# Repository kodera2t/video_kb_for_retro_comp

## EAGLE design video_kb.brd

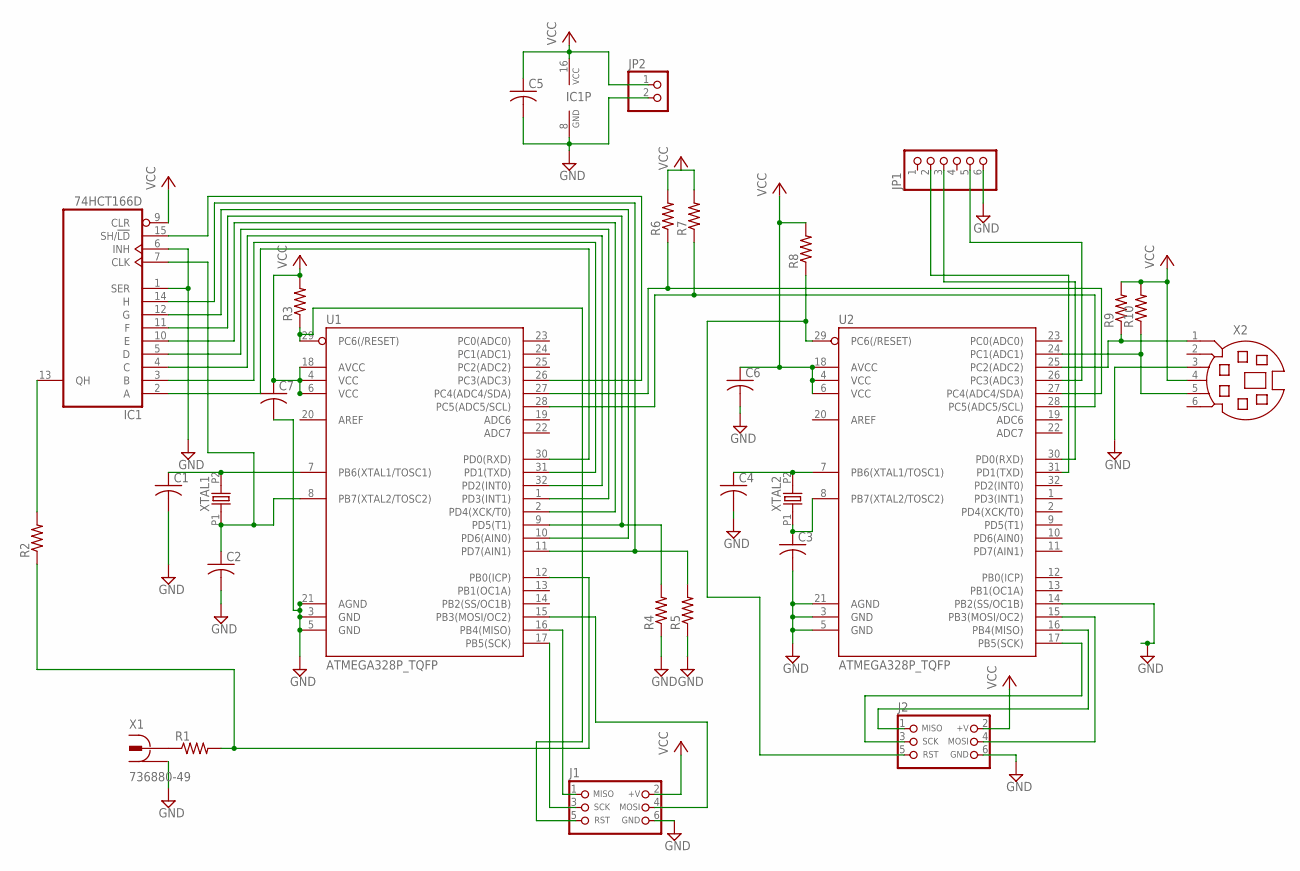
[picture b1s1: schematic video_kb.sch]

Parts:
C1, C2, C3, C4, C5, C6, C7: C-USC0603K; C0603K
IC1: 74HCT166D; SO16
J1, J2: CON_HEADER_PRG_AVR_ICSP-PTH; HEADER_PRG_2X03
JP1: HEADER-1X6; 1X06_OVAL
JP2: HEADER-1X2; 1X02_OVAL
R1, R2, R3, R4, R5, R6, R7, R8, R9, R10: R-US_R0603; R0603
U1, U2: ATMEGA328P_TQFP; TQFP32-08
X1: 736880-49
X2: MD06S; MDIN06S
XTAL1, XTAL2: OSC-XTAL-HC-49U-PTH; HC-49U-PTH

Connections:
GND: C1.2, C2.2, C3.2, C4.2, C5.2, C6.2, C7.2, IC1.1 (SER), IC1.6 (INH), IC1.8 (GND), J1.6 (GND), J2.6 (GND), JP1.6, JP2.2, R4.1, R5.1, U1.3 (GND), U1.5 (GND), U1.21 (AGND), U2.3 (GND), U2.5 (GND), U2.14 (PB2(SS/OC1B)), U2.21 (AGND), X1.1, X1.1@1 (1), X1.1@2 (1), X2.3
unnamed: C2.1, IC1.7 (CLK), U1.8 (PB7(XTAL2/TOSC2)), XTAL1.P1 (1)
unnamed: C1.1, U1.7 (PB6(XTAL1/TOSC1)), XTAL1.P2 (2)
unnamed: IC1.4 (C), U1.32 (PD2(INT0))
unnamed: IC1.5 (D), U1.1 (PD3(INT1))
unnamed: R1.2, R2.1, U1.12 (PB0(ICP))
unnamed: R1.1, X1.2
unnamed: IC1.13 (QH), R2.2
unnamed: IC1.10 (E), U1.2 (PD4(XCK/T0))
unnamed: IC1.2 (A), U1.30 (PD0(RXD))
unnamed: IC1.3 (B), U1.31 (PD1(TXD))
unnamed: IC1.11 (F), R4.2, U1.9 (PD5(T1))
unnamed: IC1.12 (G), U1.10 (PD6(AIN0))
unnamed: IC1.14 (H), R5.2, U1.11 (PD7(AIN1))
unnamed: J1.5 (RST), R3.1, U1.29 (PC6(/RESET))
unnamed: IC1.15 (SH/!LD), U1.26 (PC3(ADC3))
unnamed: R6.1, U1.27 (PC4(ADC4/SDA)), U2.27 (PC4(ADC4/SDA))
unnamed: R7.1, U1.28 (PC5(ADC5/SCL)), U2.28 (PC5(ADC5/SCL))
unnamed: J1.4 (MOSI), U1.15 (PB3(MOSI/OC2))
unnamed: C4.1, U2.7 (PB6(XTAL1/TOSC1)), XTAL2.P2 (2)
unnamed: C3.1, U2.8 (PB7(XTAL2/TOSC2)), XTAL2.P1 (1)
unnamed: J2.5 (RST), R8.1, U2.29 (PC6(/RESET))
unnamed: J2.4 (MOSI), U2.15 (PB3(MOSI/OC2))
unnamed: R9.1, U2.25 (PC2(ADC2)), X2.1
unnamed: J2.1 (MISO), U2.16 (PB4(MISO))
unnamed: J2.3 (SCK), U2.17 (PB5(SCK))
unnamed: R10.1, U2.24 (PC1(ADC1)), X2.5
unnamed: JP1.5, U2.26 (PC3(ADC3))
unnamed: JP1.3, U2.30 (PD0(RXD))
unnamed: JP1.2, U2.31 (PD1(TXD))
unnamed: J1.1 (MISO), U1.16 (PB4(MISO))
unnamed: J1.3 (SCK), U1.17 (PB5(SCK))
VCC: C5.1, C6.1, C7.1, IC1.9 (CLR), IC1.16 (VCC), J1.2 (+V), J2.2 (+V), JP2.1, R3.2, R6.2, R7.2, R8.2, R9.2, R10.2, U1.4 (VCC), U1.6 (VCC), U1.18 (AVCC), U2.4 (VCC), U2.6 (VCC), U2.18 (AVCC), X2.4

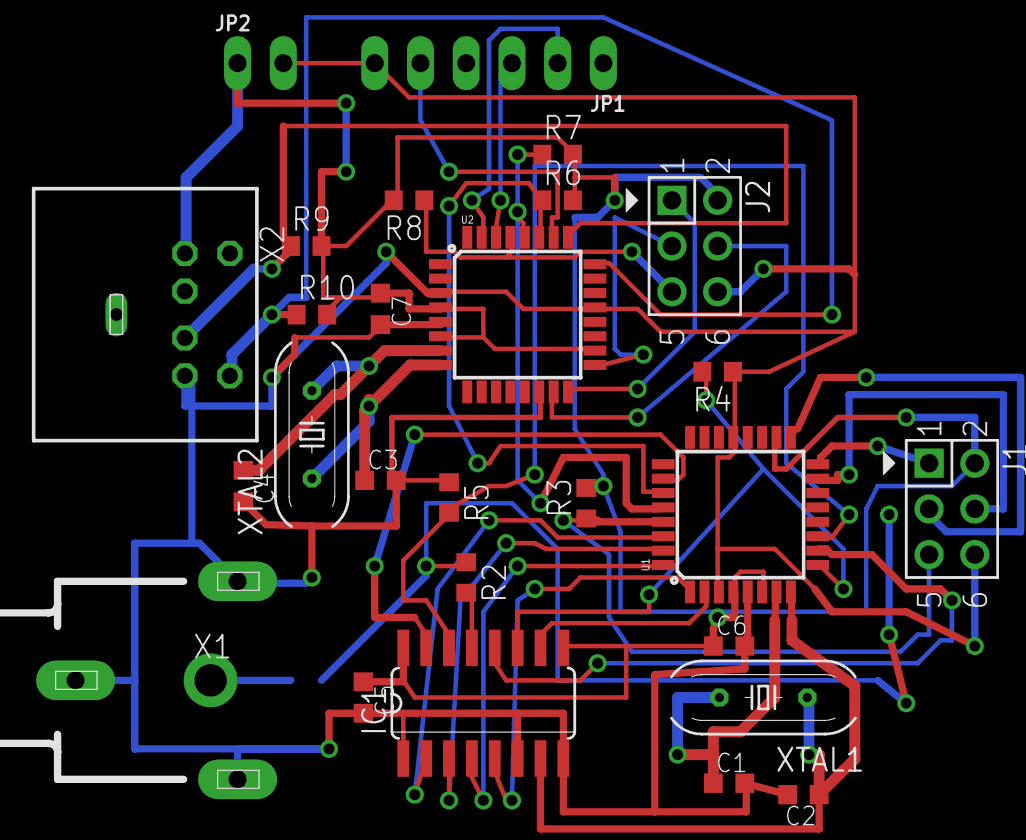
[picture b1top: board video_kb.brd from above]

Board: 2 copper layers, 28 parts (1 on the bottom side), 33 nets.

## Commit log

2015-12-05 initial submission

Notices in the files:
parts and their libraries:
SparkFun-DigitalIC: Licensing: Creative Commons ShareAlike 4.0 International - https://creativecommons.org/licenses/by-sa/4.0
microbuilder: This work is placed in the public domain, and may be freely used for commercial and non-commercial work with the following conditions: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
